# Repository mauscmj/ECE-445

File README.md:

# ECE-445
Digital Notebook for ECE 445

Partners: Max Mauschbaugh (maxjm2), Vinay Konda (konda3), and Jack Davenport (johndd2)

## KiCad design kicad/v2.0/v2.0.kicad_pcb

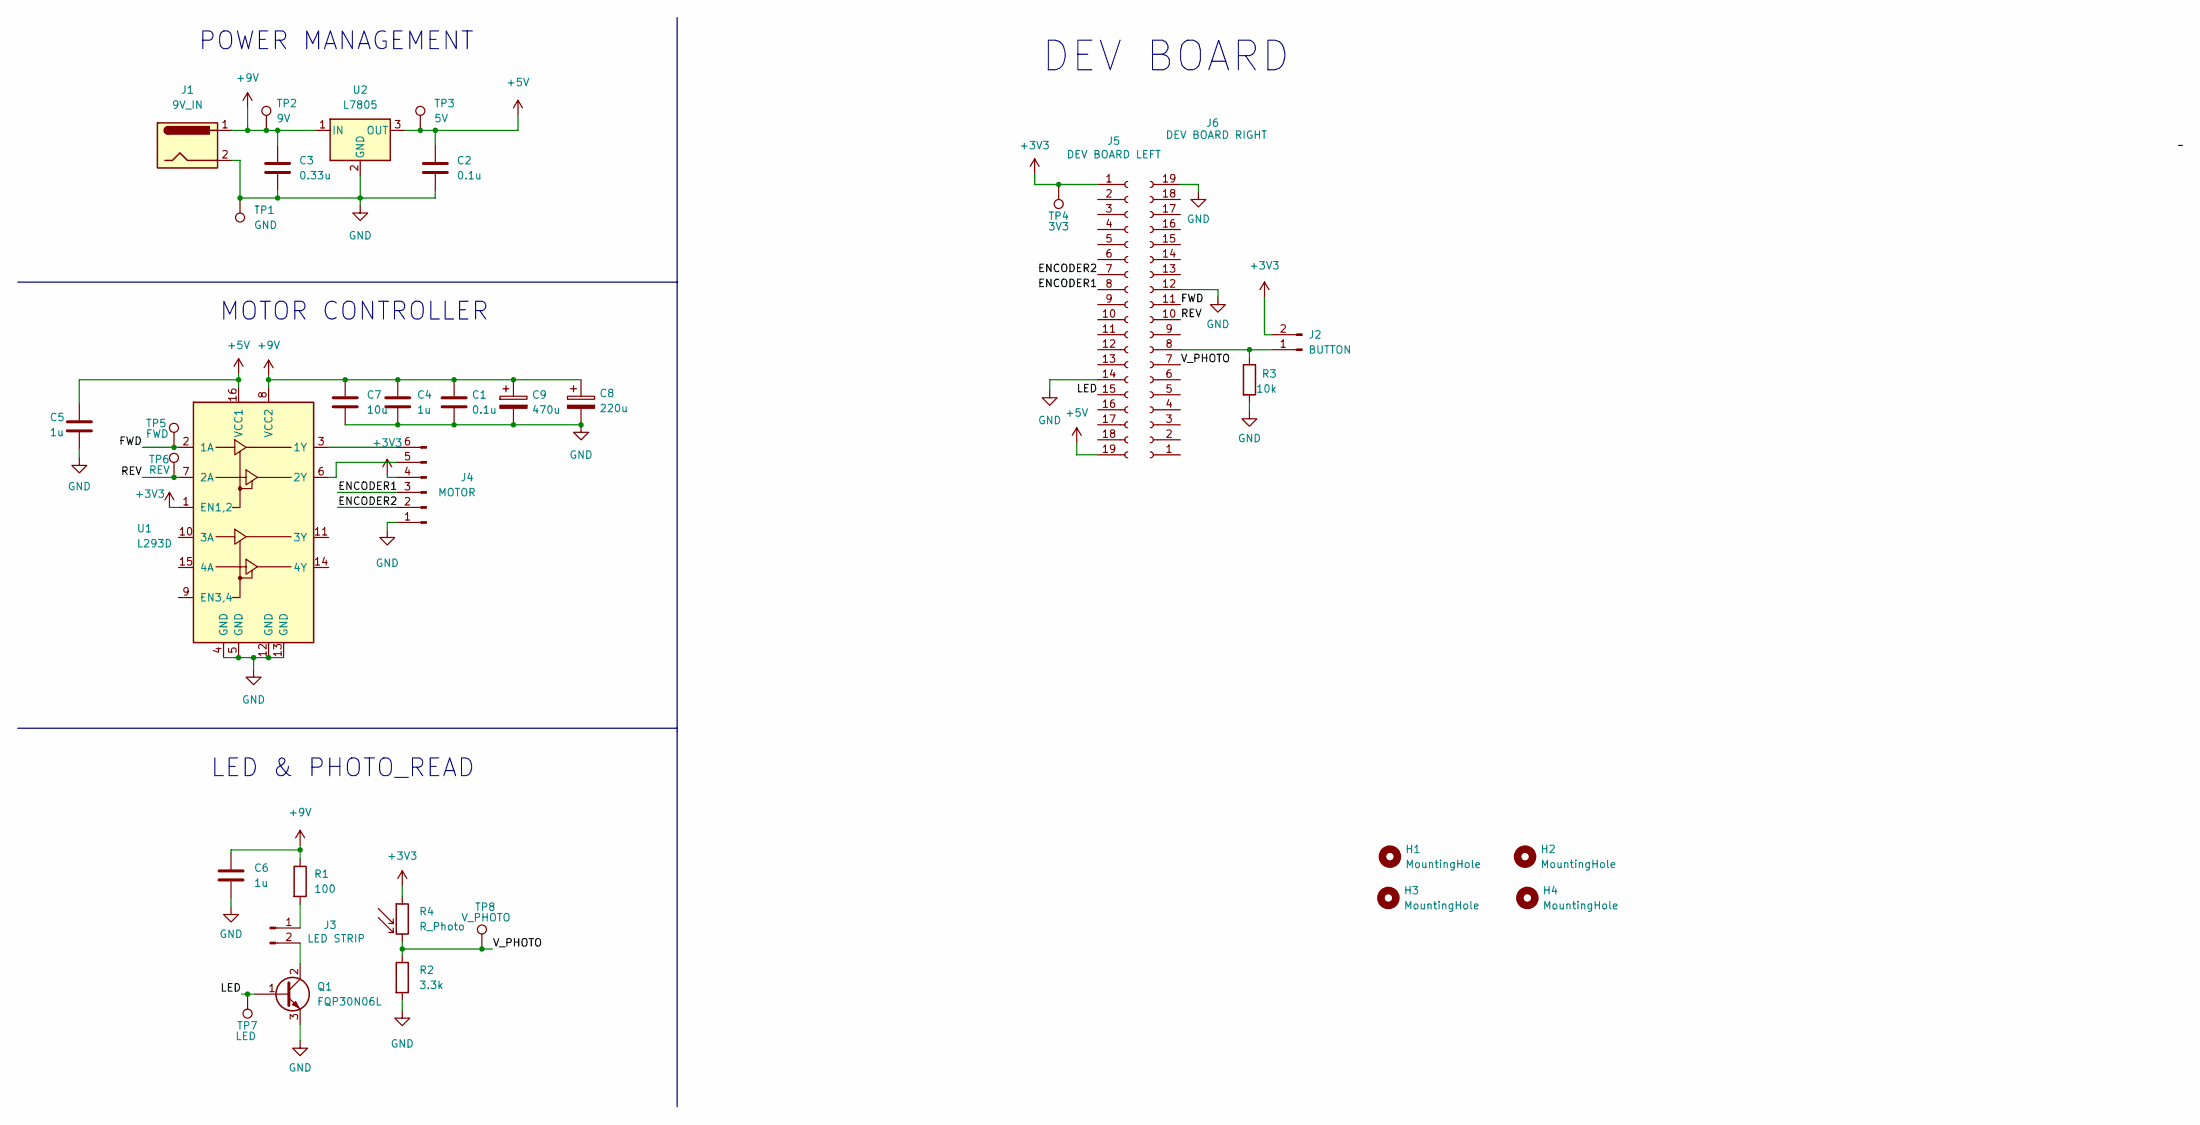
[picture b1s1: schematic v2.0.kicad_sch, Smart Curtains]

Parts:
C1, C2: 0.1u; C_0805_2012Metric_Pad1.18x1.45mm_HandSolder
C3: 0.33u; C_0805_2012Metric_Pad1.18x1.45mm_HandSolder
C4, C5, C6: 1u; C_0805_2012Metric_Pad1.18x1.45mm_HandSolder
C7: 10u; C_0805_2012Metric_Pad1.18x1.45mm_HandSolder
C8: 220u; CP_Radial_D8.0mm_P3.50mm
C9: 470u; CP_Radial_D10.0mm_P5.00mm
H1, H2, H3, H4: MountingHole; MountingHole_3.2mm_M3
J1: 9V_IN; BarrelJack_CUI_PJ-102AH_Horizontal
J2: BUTTON; Molex_KK-254_AE-6410-02A_1x02_P2.54mm_Vertical
J3: LED STRIP; Molex_KK-254_AE-6410-02A_1x02_P2.54mm_Vertical
J4: MOTOR; Molex_KK-254_AE-6410-06A_1x06_P2.54mm_Vertical
J5: DEV BOARD LEFT; PinSocket_1x19_P2.54mm_Vertical
J6: DEV BOARD RIGHT; PinSocket_1x19_P2.54mm_Vertical
Q1: FQP30N06L; TO-220-3_Vertical
R1: 100; R_0805_2012Metric_Pad1.20x1.40mm_HandSolder
R2: 3.3k; R_0805_2012Metric_Pad1.20x1.40mm_HandSolder
R3: 10k; R_0805_2012Metric_Pad1.20x1.40mm_HandSolder
R4: R_Photo; R_LDR_5.1x4.3mm_P3.4mm_Vertical
TP1: GND; TestPoint_Pad_2.5x2.5mm
TP2: 9V; TestPoint_Pad_2.5x2.5mm
TP3: 5V; TestPoint_Pad_2.5x2.5mm
TP4: 3V3; TestPoint_Pad_2.5x2.5mm
TP5: FWD; TestPoint_Pad_2.5x2.5mm
TP6: REV; TestPoint_Pad_2.5x2.5mm
TP7: LED; TestPoint_Pad_2.5x2.5mm
TP8: V_PHOTO; TestPoint_Pad_2.5x2.5mm
U1: L293D; DIP-16_W7.62mm
U2: L7805; TO-220-3_Vertical

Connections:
+3V3: J2.2, J4.4, J5.1, R4.1, TP4.1, U1.1 (EN1,2)
+5V: C2.1, C5.2, J5.19, TP3.1, U1.16 (VCC1), U2.3 (OUT)
+9V: C1.1, C3.1, C4.1, C6.1, C7.1, C8.1, C9.1, J1.1, R1.1, TP2.1, U1.8 (VCC2), U2.1 (IN)
/ENCODER1: J4.3, J5.8
/ENCODER2: J4.2, J5.7
/FWD: J6.11, TP5.1, U1.2 (1A)
/LED: J5.15, Q1.1 (B), TP7.1
/REV: J6.10, TP6.1, U1.7 (2A)
/V_PHOTO: J6.7, R2.1, R4.2, TP8.1
GND: C1.2, C2.2, C3.2, C4.2, C5.1, C6.2, C7.2, C8.2, C9.2, J1.2, J4.1, J5.14, J6.12, J6.19, Q1.3 (E), R2.2, R3.2, TP1.1, U1.4 (GND), U1.5 (GND), U1.12 (GND), U1.13 (GND), U2.2 (GND)
unnamed: J3.1, R1.2
unnamed: J3.2, Q1.2 (C)
unnamed: J4.5, U1.6 (2Y)
unnamed: J4.6, U1.3 (1Y)
unnamed: J2.1, J6.8, R3.1

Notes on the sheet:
LED & PHOTO_READ
POWER MANAGEMENT
DEV BOARD
MOTOR CONTROLLER

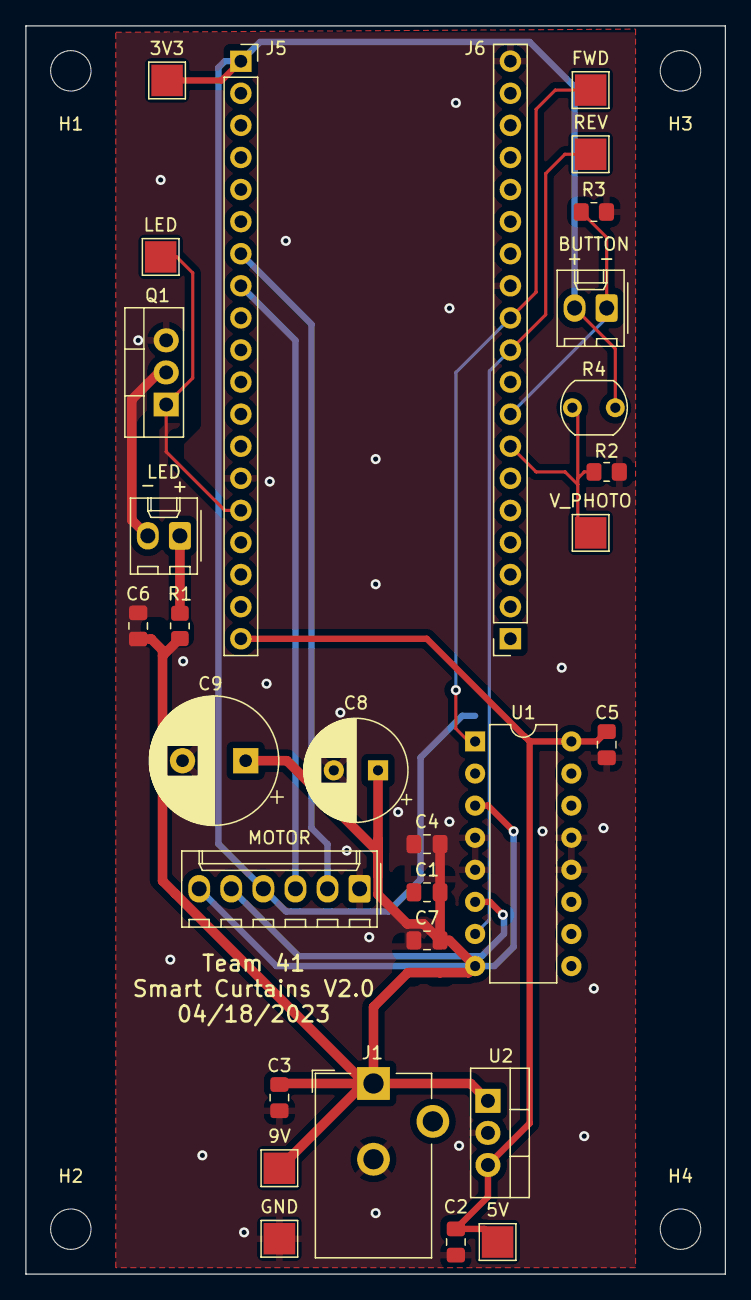
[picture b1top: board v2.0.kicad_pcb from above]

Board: 2 copper layers, 55.4 x 98.8 mm, 34 parts (0 on the bottom side), 15 nets.

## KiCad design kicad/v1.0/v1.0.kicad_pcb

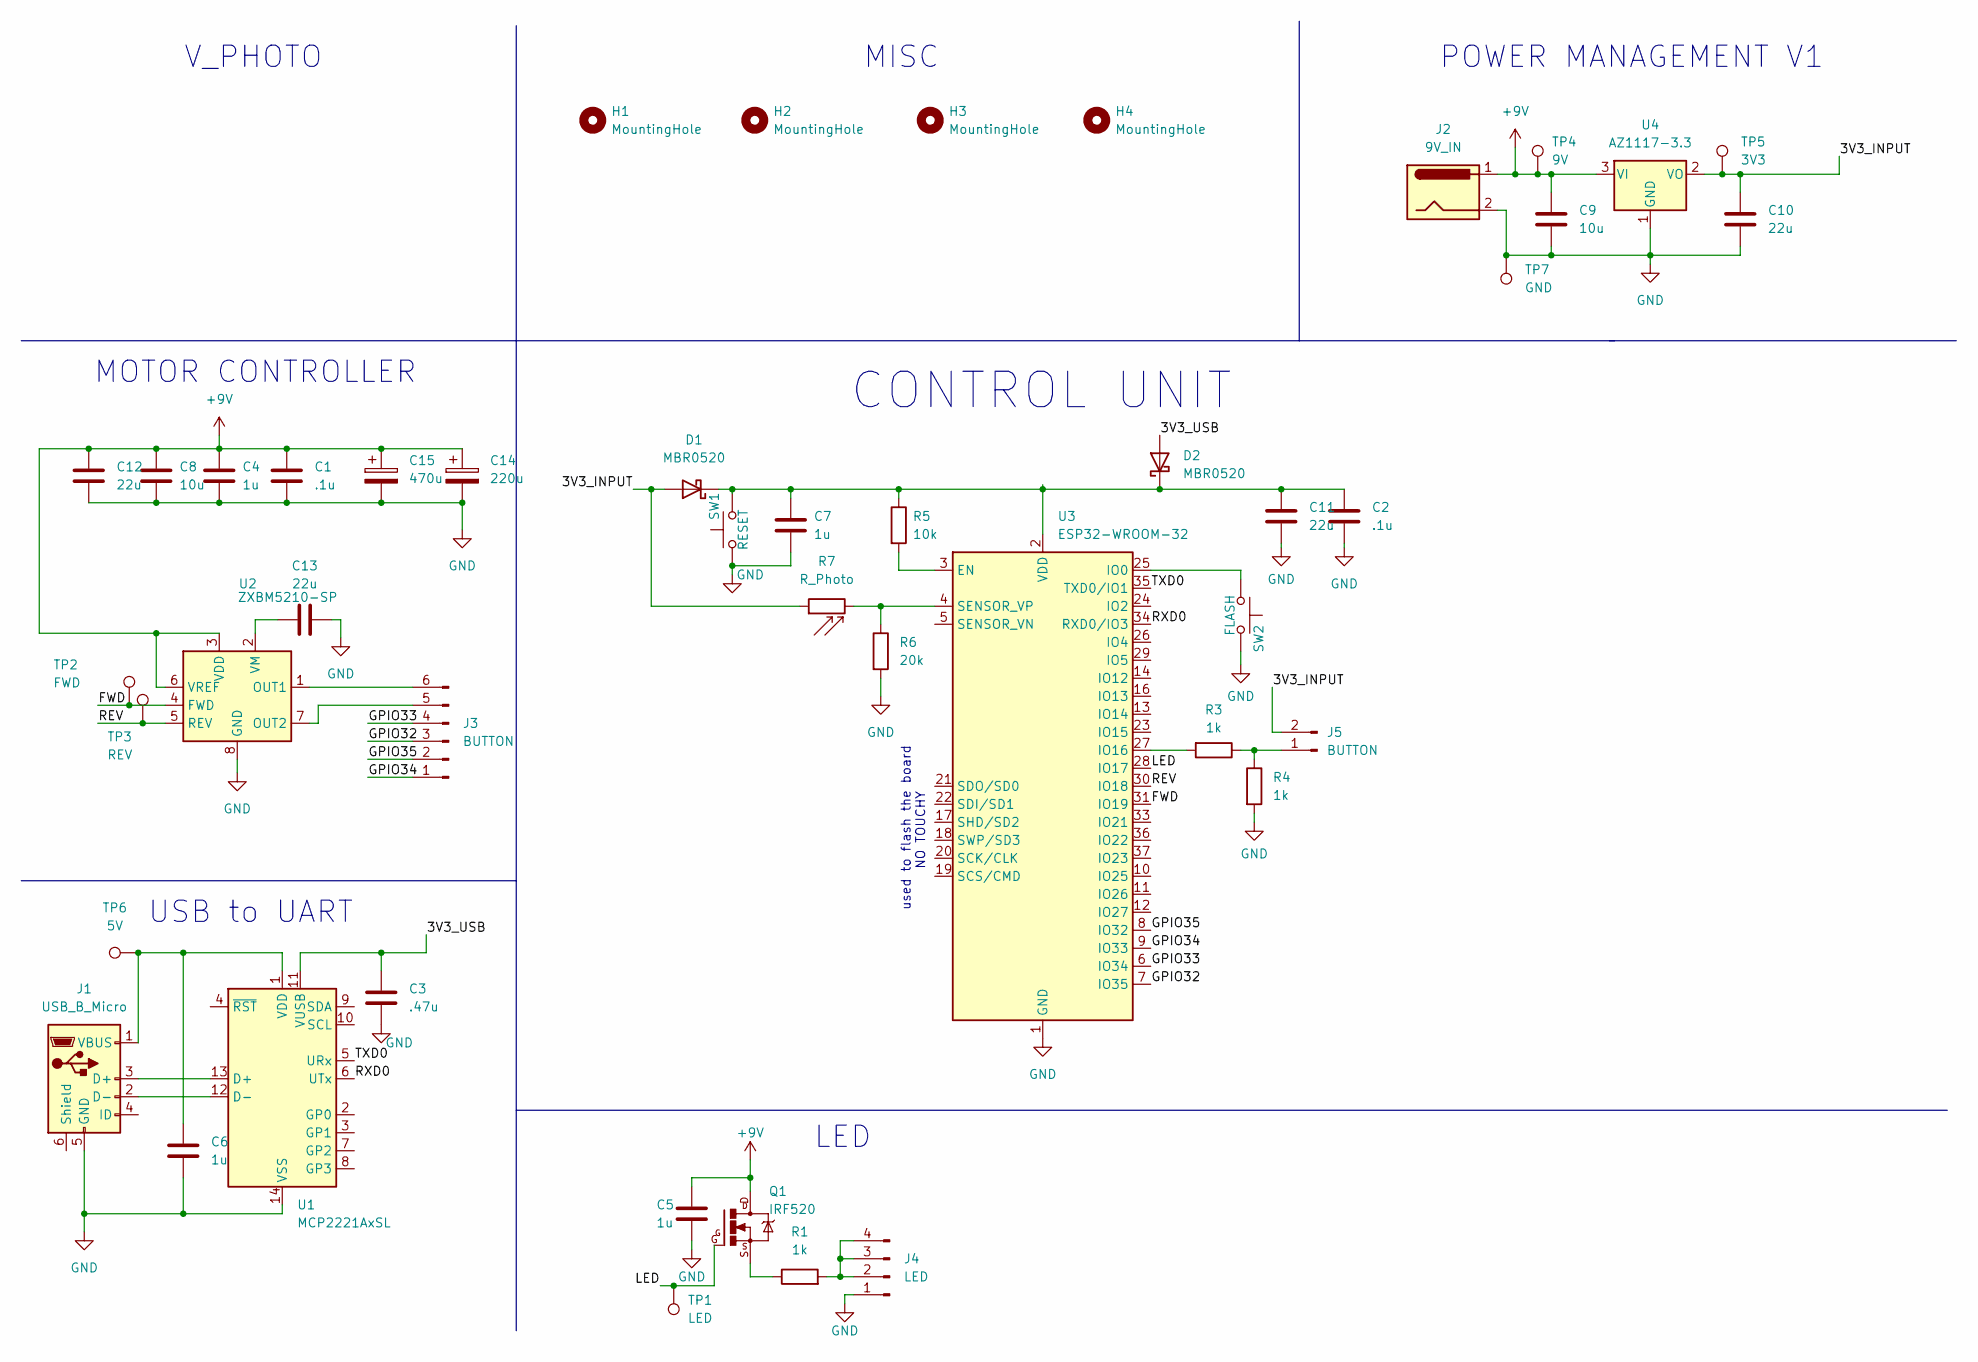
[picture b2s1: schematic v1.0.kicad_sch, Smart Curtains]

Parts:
C1, C2: .1u; C_0805_2012Metric_Pad1.18x1.45mm_HandSolder
C3: .47u; C_0805_2012Metric_Pad1.18x1.45mm_HandSolder
C4, C5, C6, C7: 1u; C_0805_2012Metric_Pad1.18x1.45mm_HandSolder
C8, C9: 10u; C_0805_2012Metric_Pad1.18x1.45mm_HandSolder
C10, C11, C12, C13: 22u; C_0805_2012Metric_Pad1.18x1.45mm_HandSolder
C14: 220u; CP_Radial_D8.0mm_P3.50mm
C15: 470u; CP_Radial_D10.0mm_P5.00mm
D1, D2: MBR0520; D_SOD-123
H1, H2, H3, H4: MountingHole; MountingHole_3.2mm_M3
J1: USB_B_Micro; USB_Micro-B_Molex-105133-0031
J2: 9V_IN; BarrelJack_CUI_PJ-102AH_Horizontal
J3: BUTTON; Molex_KK-254_AE-6410-06A_1x06_P2.54mm_Vertical
J4: LED; Molex_KK-254_AE-6410-04A_1x04_P2.54mm_Vertical
J5: BUTTON; Molex_KK-254_AE-6410-02A_1x02_P2.54mm_Vertical
Q1: IRF520; TO220BV
R1, R3, R4: 1k; R_0805_2012Metric_Pad1.20x1.40mm_HandSolder
R5: 10k; R_0805_2012Metric_Pad1.20x1.40mm_HandSolder
R6: 20k; R_0805_2012Metric_Pad1.20x1.40mm_HandSolder
R7: R_Photo; R_LDR_5.1x4.3mm_P3.4mm_Vertical
SW1: RESET; SW_PUSH_6mm
SW2: FLASH; SW_PUSH_6mm
TP1: LED; TestPoint_Pad_2.5x2.5mm
TP2: FWD; TestPoint_Pad_2.5x2.5mm
TP3: REV; TestPoint_Pad_2.5x2.5mm
TP4: 9V; TestPoint_Pad_2.5x2.5mm
TP5: 3V3; TestPoint_Pad_2.5x2.5mm
TP6: 5V; TestPoint_Pad_2.5x2.5mm
TP7: GND; TestPoint_Pad_2.5x2.5mm
U1: MCP2221AxSL; SOIC-14_3.9x8.7mm_P1.27mm
U2: ZXBM5210-SP; Diodes_SO-8EP
U3: ESP32-WROOM-32
U4: AZ1117-3.3; SOT-89-3_Handsoldering

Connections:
+9V: C1.1, C4.1, C5.1, C8.1, C9.1, C12.1, C14.1, C15.1, J2.1, Q1.D, TP4.1, U2.3 (VDD), U2.6 (VREF), U4.3 (VI)
/3V3_INPUT: C10.1, D1.2 (A), J5.2, R7.1, TP5.1, U4.2 (VO)
/3V3_USB: C3.1, D2.2 (A), U1.11 (VUSB)
/FWD: TP2.1, U2.4 (FWD), U3.31 (IO19)
/GPIO32: J3.3, U3.7 (IO35)
/GPIO33: J3.4, U3.6 (IO34)
/GPIO34: J3.1, U3.9 (IO33)
/GPIO35: J3.2, U3.8 (IO32)
/LED: Q1.G, TP1.1, U3.28 (IO17)
/REV: TP3.1, U2.5 (REV), U3.30 (IO18)
/RXD0: U1.6 (UTx), U3.34 (RXD0/IO3)
/TXD0: U1.5 (URx), U3.35 (TXD0/IO1)
GND: C1.2, C2.2, C3.2, C4.2, C5.2, C6.2, C7.2, C8.2, C9.2, C10.2, C11.2, C12.2, C13.2, C14.2, C15.2, J1.5 (GND), J2.2, J4.1, R4.2, R6.2, SW1.1, SW2.2, TP7.1, U1.14 (VSS), U2.8 (GND), U2.9 (GND), U3.1 (GND), U3.15 (GND), U3.38 (GND), U3.39 (GND), U4.1 (GND)
unnamed: C6.1, J1.1 (VBUS), TP6.1, U1.1 (VDD)
unnamed: C2.1, C7.1, C11.1, D1.1 (K), D2.1 (K), R5.1, SW1.2, U3.2 (VDD)
unnamed: C13.1, U2.2 (VM)
unnamed: J1.2 (D-), U1.12 (D-)
unnamed: J1.3 (D+), U1.13 (D+)
unnamed: J3.5, U2.7 (OUT2)
unnamed: J3.6, U2.1 (OUT1)
unnamed: J4.2, J4.3, J4.4, R1.2
unnamed: J5.1, R3.1, R4.1
unnamed: Q1.S, R1.1
unnamed: R3.2, U3.27 (IO16)
unnamed: R5.2, U3.3 (EN)
unnamed: R6.1, R7.2, U3.4 (SENSOR_VP)
unnamed: SW2.1, U3.25 (IO0)

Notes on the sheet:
V_PHOTO
used to flash the board NO TOUCHY
LED
POWER MANAGEMENT V1
CONTROL UNIT
MOTOR CONTROLLER
MISC
USB to UART

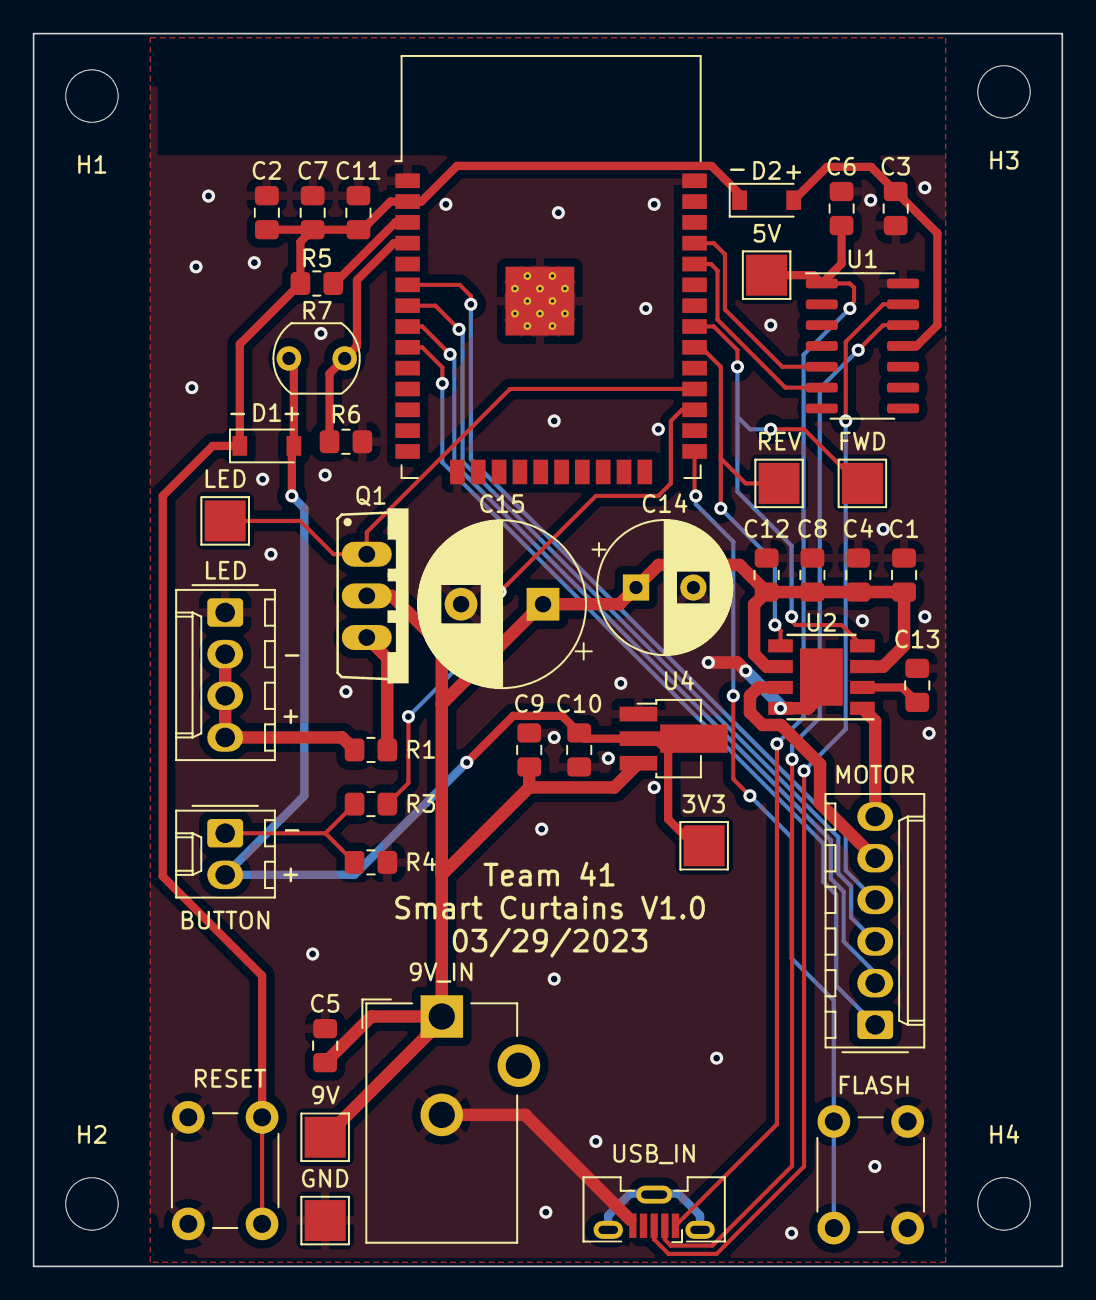
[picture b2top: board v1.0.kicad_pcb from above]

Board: 2 copper layers, 62.7 x 75.2 mm, 46 parts (0 on the bottom side), 27 nets.

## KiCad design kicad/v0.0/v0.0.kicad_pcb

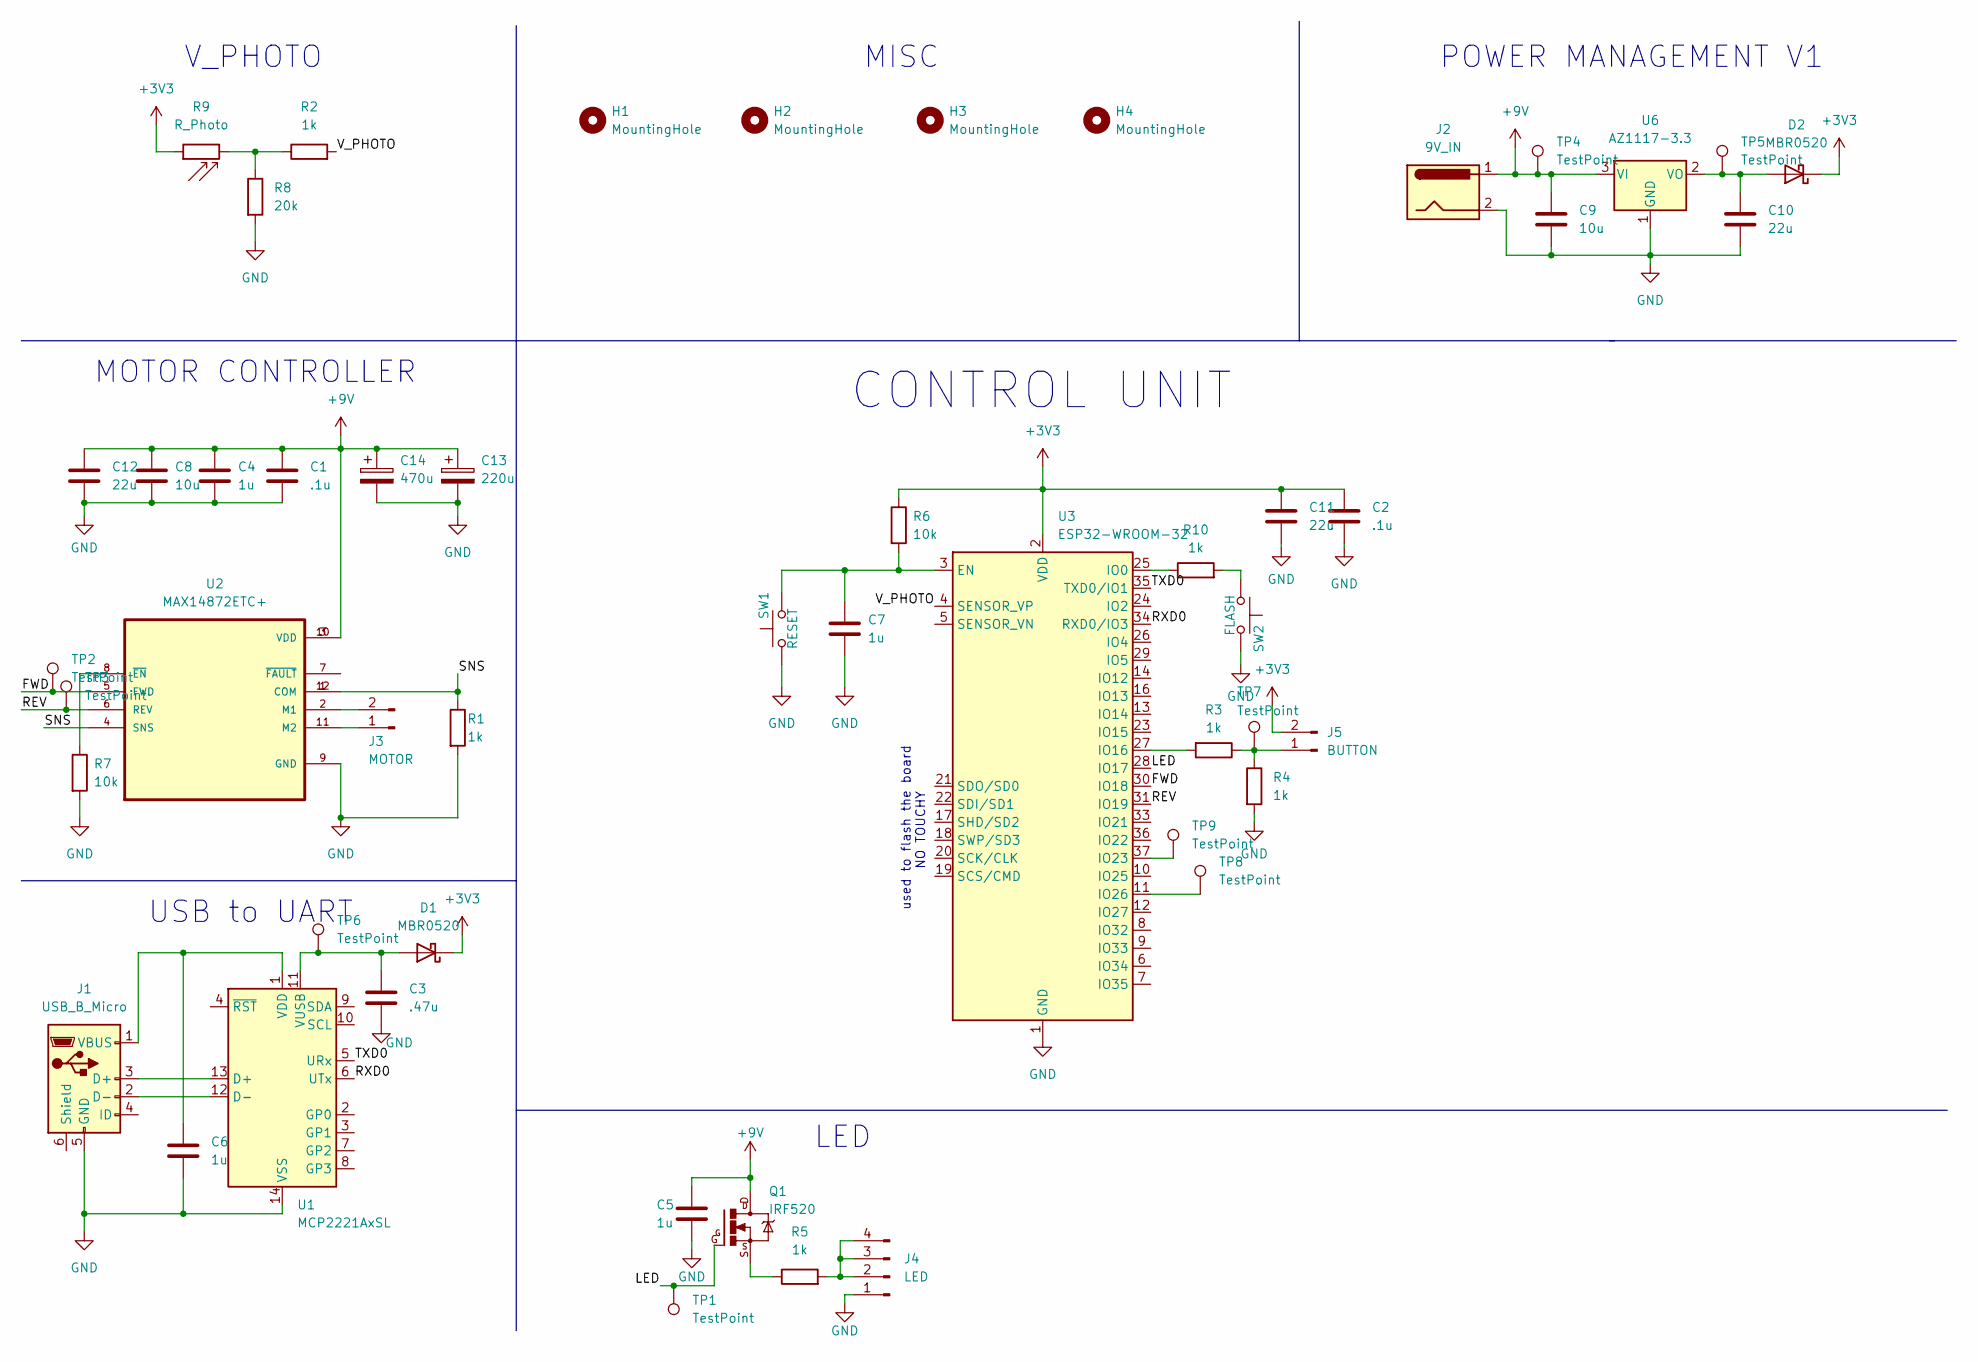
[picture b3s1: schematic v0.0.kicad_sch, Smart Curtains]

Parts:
C1, C2: .1u; C_0805_2012Metric_Pad1.18x1.45mm_HandSolder
C3: .47u; C_0805_2012Metric_Pad1.18x1.45mm_HandSolder
C4, C5, C6, C7: 1u; C_0805_2012Metric_Pad1.18x1.45mm_HandSolder
C8, C9: 10u; C_0805_2012Metric_Pad1.18x1.45mm_HandSolder
C10, C11, C12: 22u; C_0805_2012Metric_Pad1.18x1.45mm_HandSolder
C13: 220u; CP_Radial_D8.0mm_P3.50mm
C14: 470u; CP_Radial_D10.0mm_P5.00mm
D1, D2: MBR0520; D_SOD-123
H1, H2, H3, H4: MountingHole; MountingHole_3.2mm_M3
J1: USB_B_Micro; USB_Micro-B_Molex-105133-0031
J2: 9V_IN; BarrelJack_CUI_PJ-102AH_Horizontal
J3: MOTOR; Molex_KK-254_AE-6410-02A_1x02_P2.54mm_Vertical
J4: LED; Molex_KK-254_AE-6410-04A_1x04_P2.54mm_Vertical
J5: BUTTON; Molex_KK-254_AE-6410-02A_1x02_P2.54mm_Vertical
Q1: IRF520; TO220BV
R1, R2, R3, R4, R5, R10: 1k; R_0805_2012Metric_Pad1.20x1.40mm_HandSolder
R6, R7: 10k; R_0805_2012Metric_Pad1.20x1.40mm_HandSolder
R8: 20k; R_0805_2012Metric_Pad1.20x1.40mm_HandSolder
R9: R_Photo; R_LDR_5.1x4.3mm_P3.4mm_Vertical
SW1: RESET; SW_PUSH-12mm_Wuerth-430476085716
SW2: FLASH; SW_PUSH-12mm_Wuerth-430476085716
TP1, TP2, TP3, TP4, TP5, TP6, TP7, TP8, TP9: TestPoint; TestPoint_Pad_2.5x2.5mm
U1: MCP2221AxSL; SOIC-14_3.9x8.7mm_P1.27mm
U2: MAX14872ETC+; SON50P300X300X80-13N
U3: ESP32-WROOM-32
U6: AZ1117-3.3; SOT-223

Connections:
+3V3: C2.1, C11.1, D1.1 (K), D2.1 (K), J5.2, R6.1, R9.1, U3.2 (VDD)
+9V: C1.1, C4.1, C5.1, C8.1, C9.1, C12.1, C13.1, C14.1, J2.1, Q1.D, TP4.1, U2.3 (VDD), U2.10 (VDD), U6.3 (VI)
/FWD: TP2.1, U2.5 (FWD), U3.30 (IO18)
/LED: Q1.G, TP1.1, U3.28 (IO17)
/REV: TP3.1, U2.6 (REV), U3.31 (IO19)
/RXD0: U1.6 (UTx), U3.34 (RXD0/IO3)
/SNS: R1.1, U2.1 (COM), U2.4 (SNS), U2.12 (COM)
/TXD0: U1.5 (URx), U3.35 (TXD0/IO1)
/V_PHOTO: R2.2, U3.4 (SENSOR_VP)
GND: C1.2, C2.2, C3.2, C4.2, C5.2, C6.2, C7.2, C8.2, C9.2, C10.2, C11.2, C12.2, C13.2, C14.2, J1.5 (GND), J2.2, J4.1, R1.2, R4.2, R7.2, R8.2, SW1.1, SW2.2, U1.14 (VSS), U2.9 (GND), U3.1 (GND), U3.15 (GND), U3.38 (GND), U3.39 (GND), U6.1 (GND)
unnamed: C3.1, D1.2 (A), TP6.1, U1.11 (VUSB)
unnamed: C6.1, J1.1 (VBUS), U1.1 (VDD)
unnamed: C7.1, R6.2, SW1.2, U3.3 (EN)
unnamed: C10.1, D2.2 (A), TP5.1, U6.2 (VO)
unnamed: J1.2 (D-), U1.12 (D-)
unnamed: J1.3 (D+), U1.13 (D+)
unnamed: J3.1, U2.11 (M2)
unnamed: J3.2, U2.2 (M1)
unnamed: J4.2, J4.3, J4.4, R5.2
unnamed: J5.1, R3.1, R4.1, TP7.1
unnamed: Q1.S, R5.1
unnamed: R2.1, R8.1, R9.2
unnamed: R3.2, U3.27 (IO16)
unnamed: R7.1, U2.8 (~EN)
unnamed: R10.2, SW2.1
unnamed: TP8.1, U3.11 (IO26)
unnamed: TP9.1, U3.37 (IO23)
unnamed: R10.1, U3.25 (IO0)

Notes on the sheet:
V_PHOTO
used to flash the board NO TOUCHY
LED
POWER MANAGEMENT V1
CONTROL UNIT
MOTOR CONTROLLER
MISC
USB to UART

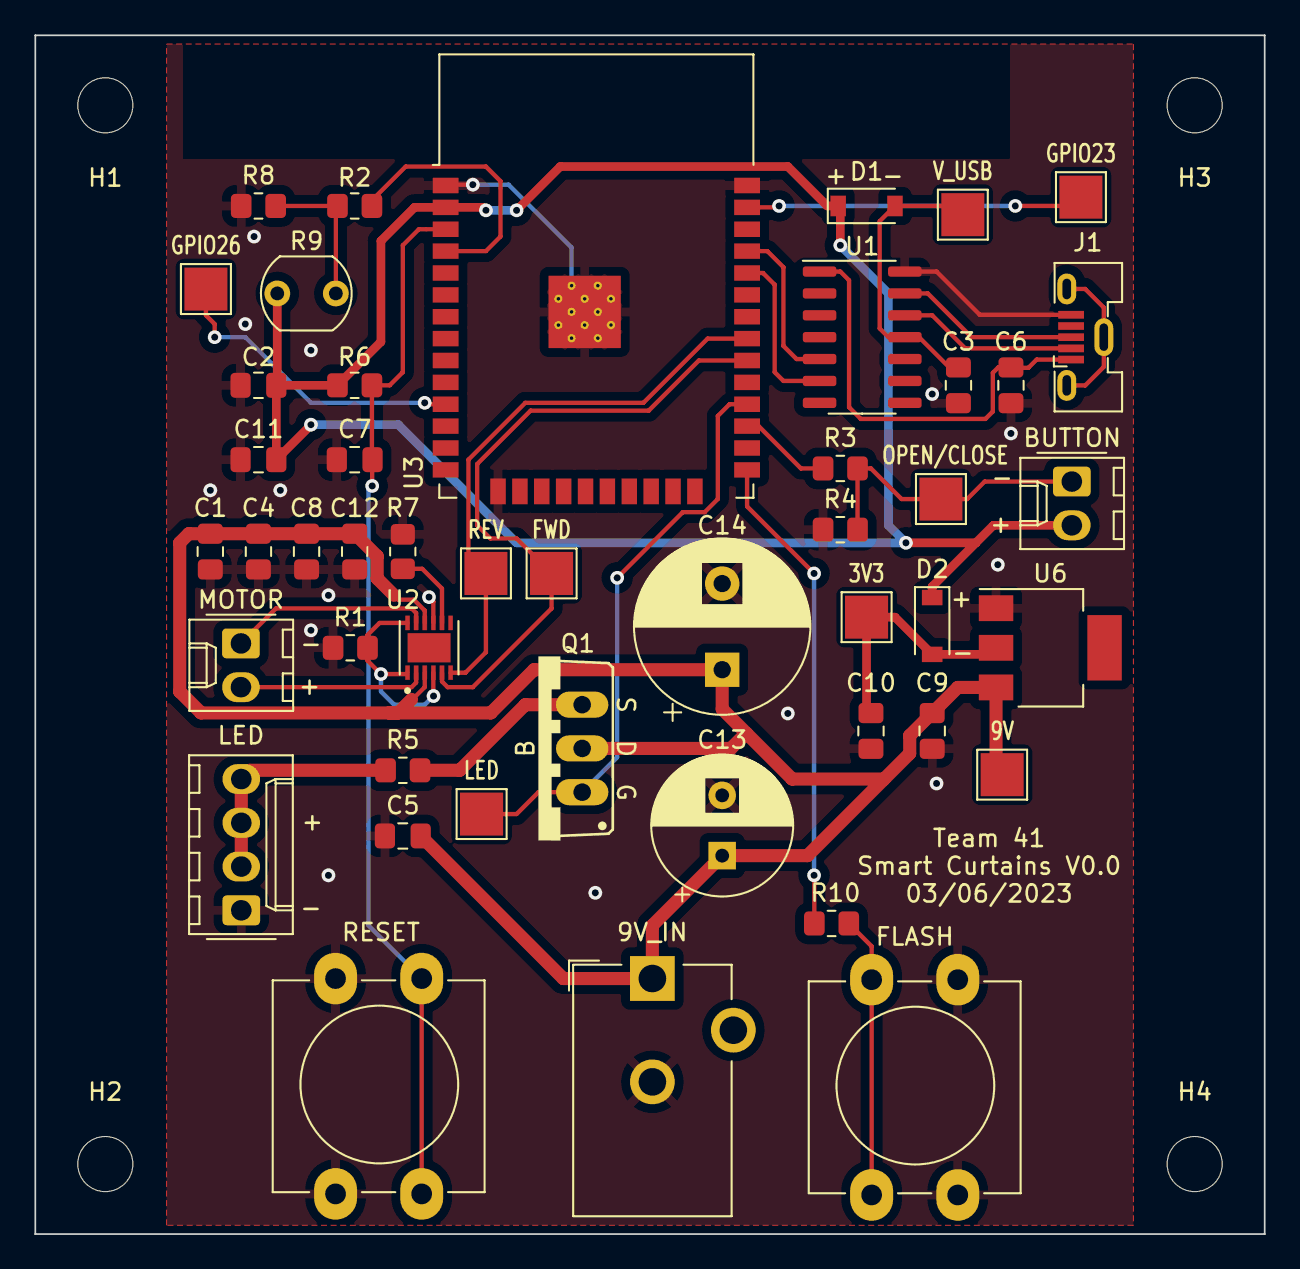
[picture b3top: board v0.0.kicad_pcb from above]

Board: 2 copper layers, 71.4 x 69.6 mm, 51 parts (0 on the bottom side), 28 nets.

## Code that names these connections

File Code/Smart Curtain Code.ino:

#include <WiFi.h>
#include <FS.h>
#include <SPIFFS.h>

const char* ssid     = "501Healey21";
const char* password = "fancywindow523";

const int identity_led = 2;
const int led_gpio = 23;
const int FWD = 5; // d0
const int REV = 18; // d1
const int LED = 13; // d2
const int BUTTON = 16; //d3
const int PHOTO = 39; // Analog in 
const int ENCODER1 = 32;
const int ENCODER2 = 33;
int curr_loc = 0;
int sensorValue = 0;

const bool switchOn  = false;     // using INPUT_PULLUP
const bool switchOff = true;

bool lastState   = switchOff;
bool newState    = switchOff;
bool toggleState = false;

extern "C" {
#include "homeintegration.h"
}
homekit_service_t* hapservice = {0};
String pair_file_name = "/pair.dat";
// homekit_characteristic_t * ch_current_pos= NULL;

void setup() {
  Serial.begin(115200);
  delay(10);
  pinMode(REV,OUTPUT);
  pinMode(FWD,OUTPUT);

  // Mount SPIFFS file system
  if (!SPIFFS.begin(true)) {
    Serial.print("SPIFFS mount failed");
  }

  // Connect to WiFi network
  Serial.println();
  Serial.print("Connecting to ");
  Serial.println(ssid);

  WiFi.begin(ssid, password);

  while (WiFi.status() != WL_CONNECTED) {
    delay(500);
    Serial.print(".");
  }
  Serial.println("");
  Serial.println("WiFi connected");
  Serial.println("IP address: ");
  Serial.println(WiFi.localIP());

  pinMode(led_gpio, OUTPUT);
  pinMode(LED,OUTPUT);
  pinMode(BUTTON,INPUT_PULLUP);
  pinMode(PHOTO,INPUT);
  pinMode(ENCODER1,INPUT);
  pinMode(ENCODER2,INPUT);
  
  ///setup identity gpio
  hap_set_identity_gpio(identity_led);    //identity_led=2 will blink on identity

  /// now will setup homekit device

  //this is for custom storage usage
  // In given example we are using \pair.dat file in our SPIFFS system
  //see implementation below
  init_hap_storage();
  set_callback_storage_change(storage_changed);

  /// We will use for this example only one accessory (possible to use a several on the same ESP)
  //Our accessory type is light bulb, Apple interface will proper show that
  hap_setbase_accessorytype(homekit_accessory_category_window_covering);

  /// init base properties
  hap_initbase_accessory_service("hosta", "Yurik72a", "01", "EspHapLed2", "2.0");
  //we will add only one light bulb service and keep pointer for nest using
  hapservice = hap_add_windowcovering_service("Led", led_callback, (void*)&led_gpio);
  // ch_current_pos= homekit_service_characteristic_by_type(hapservice, HOMEKIT_CHARACTERISTIC_CURRENT_POSITION);
  // INIT_CHARACHTERISTIC_VAL(int,ch_current_pos,100);

  //and finally init HAP
  hap_init_homekit_server();

  attachInterrupt(digitalPinToInterrupt(ENCODER1), encoder_isr, CHANGE);
  loop();
}

void loop() {
  // put your main code here, to run repeatedly:
  Flip();
  sensorValue = analogRead(PHOTO);
 // Serial.println("sensorValue: " + String(sensorValue));
  if(toggleState == false) {
    if(curr_loc >= -450) {
      set_motor(0);
      toggleState = true;
    }
    else{
      set_motor(100);
      toggleState = true;
    }
  }
  if(curr_loc >= -75 && sensorValue <= 500) {
    // Serial.println("sensorValue: " + String(sensorValue));
    digitalWrite(LED, HIGH);
  }
  else {
    digitalWrite(LED, LOW);
  }
  delay(50);
}

void init_hap_storage() {
  Serial.print("init_hap_storage");
  File fsDAT = SPIFFS.open(pair_file_name, "r");
  if (!fsDAT) {
    Serial.println("Failed to read file pair.dat");
    return;
  }
  int size = hap_get_storage_size_ex();
  char* buf = new char[size];
  memset(buf, 0xff, size);
  int readed = fsDAT.readBytes(buf, size);
  Serial.print("Readed bytes ->");
  Serial.println(readed);
  hap_init_storage_ex(buf, size);
  fsDAT.close();
  delete []buf;
}

void storage_changed(char * szstorage, int size) {
  SPIFFS.remove(pair_file_name);
  File fsDAT = SPIFFS.open(pair_file_name, "w+");
  if (!fsDAT) {
    Serial.println("Failed to open pair.dat");
    return;
  }
  fsDAT.write((uint8_t*)szstorage, size);
  fsDAT.close();
}

//can be used for any logic, it will automatically inform Apple Home app about state changes
void set_motor(int val) {
  Serial.println("set_led");
  Rotate_motor(100 - val);
  //we need notify apple about changes
  if (hapservice) {
    Serial.println("notify hap");
    //getting on/off characteristic
    // HAP_NOTIFY_CHANGES(int, ch_current_pos, val,0)
    homekit_characteristic_t * ch = homekit_service_characteristic_by_type(hapservice, HOMEKIT_CHARACTERISTIC_ON);
    if (ch) {
      Serial.println("found characteristic");
      if (ch->value.int_value != val) { //will notify only if different
        ch->value.int_value = val;
        homekit_characteristic_notify(ch, ch->value);
      }
    }
  }
}

void Rotate_motor(int target_location) {
  Serial.println(String(curr_loc) + " before");
  if(curr_loc > -900 * 0.01 * target_location) {
    while(curr_loc >= -900 * 0.01 * target_location ) {
      analogWrite(FWD, 0);    // rotate down
      analogWrite(REV, 200);
    }
    // toggleState = true;
  }
  else if(curr_loc < -900 * 0.01 * target_location) {
      while(curr_loc <= -900 * 0.01 * target_location) {
      analogWrite(FWD, 255);
      analogWrite(REV, 0);
    }
    // toggleState = true;
  }
  analogWrite(FWD, 0);
  analogWrite(REV, 0);
}

void encoder_isr() {
  // Reading the current state of encoder A and B
  int A = digitalRead(ENCODER1);
  int B = digitalRead(ENCODER2);
  // If the state of A changed, it means the encoder has been rotated
  if ((A == HIGH) != (B == LOW)) {
    curr_loc--;
  } else {
    curr_loc++;
  }
}

void Flip() {
  newState = digitalRead(BUTTON);

  if( lastState != newState ) // state changed
  {
    delay(5);
    lastState = newState;
    
    // push on, push off
    if( newState == switchOn && toggleState == false )
    {
      toggleState = true;
    //  Serial.println( F ( "Switched ON" ) );
    }
    else if( newState == switchOn && toggleState == true )
    {
      toggleState = false;
     // Serial.println( F ( "Switched OFF" ) );
    }
  }
}

void led_callback(homekit_characteristic_t *ch, homekit_value_t value, void *context) {
  Serial.println("led_callback");
  Serial.println(value.int_value);
  set_motor(ch->value.int_value);
}

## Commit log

2023-02-07 Create Max Notes
2023-02-07 Create Max Notes Folder
2023-02-07 Create Vinay Notes
2023-02-07 Create Jack Notes
2023-02-07 Create code
2023-02-09 Create Drawing
2023-02-09 deleted jack notes and added kicad folder for schematics and pcb design including v0.0
2023-02-09 test
2023-02-09 removing some folders, updated motor IC schematic with incomplete PWM
2023-02-09 PWM v0.0 done
2023-02-09 im an idjit
2023-02-22 kicad stuff
2023-02-22 v0.0 is done (i think)! also added a Documents folder to store datasheets and such
2023-02-22 deleting some junk
2023-02-22 forgot to save in kicad before sending files here... awk
2023-02-22 updated motor to be 9V
2023-02-23 Add files via upload
    v0 pics
2023-02-23 all footprints assigned except for potentiometer
2023-02-23 added some footprints I had to download to Documents
2023-02-23 finally found some pot
2023-02-24 sorted the pcb design, will wire it up if monday with the TA goes well
2023-02-28 shes a beaut
2023-03-01 ready to design PCB
2023-03-01 forgot to save | ready to design PCB
2023-03-05 ab to start pcb design
2023-03-06 pcb is laid out, time to route
2023-03-06 minor tweaks, im a lil bit of a control freak so i keep messing wit it
2023-03-06 pcb v1
2023-03-06 some throwaway changes git is making me commit
2023-03-06 more files
2023-03-06 removed ground
2023-03-06 made resistors and capacitors standard size
2023-03-07 blah
2023-03-07 mBRO diodes now
2023-03-07 mbro isnt being such a bro
2023-03-07 general layout ready to be finalized
2023-03-07 v1.0 is done
2023-03-07 ready for board review/ordering
2023-03-07 v0.0 has been sent to TA for printing, all future changes must be on v1.0
2023-03-08 v0.0 pcb checkin
2023-03-08 final versions I sent to TA, signing off for the week now
2023-03-28 getting ready to start designing PCB 1.0
2023-03-29 PCB v1.0 is designed and sent to Nikhil, don't modify anything in here anymore
2023-03-29 some schematic cleaning/ making v2.0 for the next round
2023-04-17 v2.0 is done
2023-04-17 added some ground stitching and slight rearrangements to v2.0
2023-04-17 final schematic
2023-04-19 minor changes to pcb
2023-04-30 Update Vinay Notes
2023-04-30 final commit of the semester
2023-05-02 code
2023-05-02 Create a
2023-05-03 Update README.md
    testing formatting
2023-05-04 Rename Max Notes Folder ./README.md to Max Notes/README.md
2023-05-04 final repository clean up
